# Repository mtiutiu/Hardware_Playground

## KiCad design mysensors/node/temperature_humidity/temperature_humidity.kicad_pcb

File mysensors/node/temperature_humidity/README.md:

#### Mysensors RFM69 temperature & humidity node

##### 3D renderings of pcb

Top view | Bottom view
------------ | -------------
 |

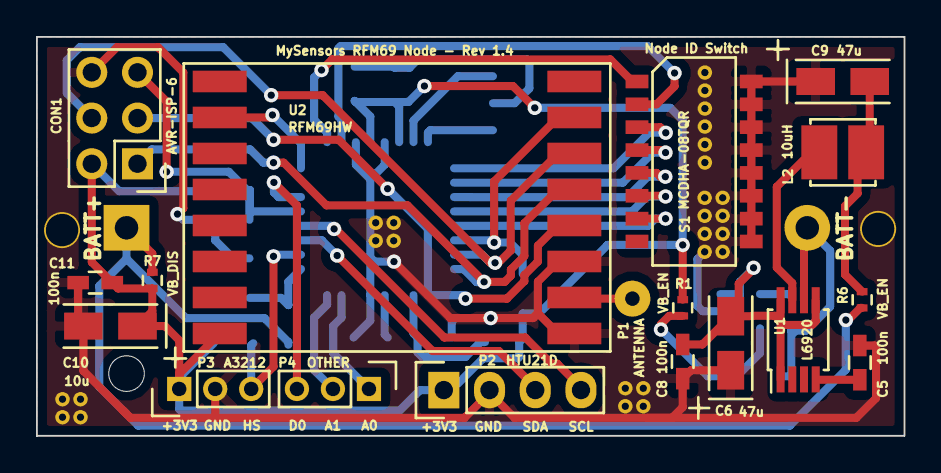
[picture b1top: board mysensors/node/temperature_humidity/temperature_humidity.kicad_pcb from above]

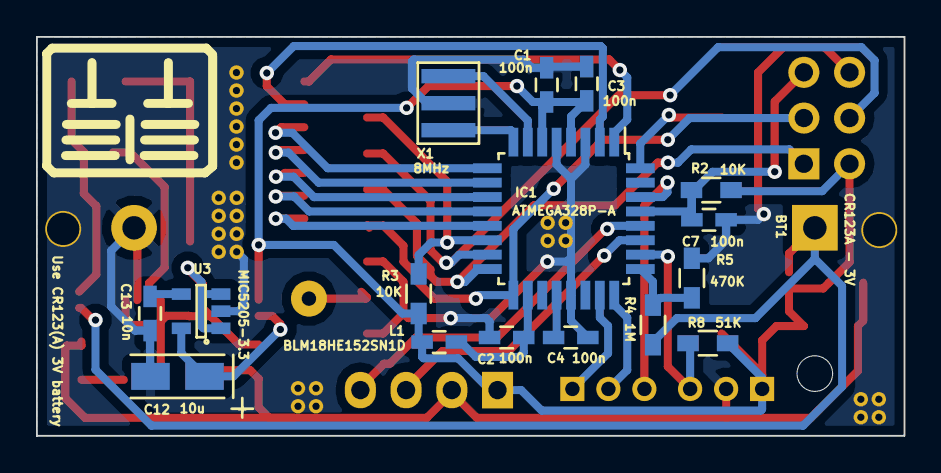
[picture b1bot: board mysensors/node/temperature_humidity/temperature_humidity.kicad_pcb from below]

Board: 2 copper layers, 48.2 x 22.2 mm, 35 parts (17 on the bottom side), 34 nets.

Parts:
BT1: CR123A - 3V; CR123_holder
C1, C2, C3, C4, C5, C7, C8, C11: 100n; C_0603_HandSoldering
C6, C9: 47u; TantalC_SizeA_EIA-3216_Wave
C10, C12: 10u; TantalC_SizeA_EIA-3216_Wave
C13: 10n; C_0603_HandSoldering
CON1: AVR-ISP-6; Pin_Header_Straight_2x03
IC1: ATMEGA328P-A; TQFP-32_7x7mm_Pitch0.8mm
L1: BLM18HE152SN1D; C_0603_HandSoldering
L2: 10uH; DLJ-3015
P1: ANTENNA; SolderWirePad_single_0-8mmDrill
P2: HTU21D; Pin_Header_Straight_1x04
P3: A3212; Pin_Header_Straight_1x03_Pitch2.00mm
P4: OTHER; Pin_Header_Straight_1x03_Pitch2.00mm
R1, R6: VB_EN; R_0402
R2, R3: 10K; R_0603_HandSoldering
R4: 1M; R_0603_HandSoldering
R5: 470K; R_0603_HandSoldering
R7: VB_DIS; R_0402
R8: 51K; R_0603_HandSoldering
S1: MCDHA-08TQR; DIPSWITCH_SMD_1.27-16
U1: L6920; MSOP-8_3x3mm_Pitch0.65mm
U2: RFM69HW; RFM69HW_SMD_Handsoldering
U3: MIC5205-3.3; SOT-23-5
X1: 8MHz; ZTTCR-3

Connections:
+3V3: C1.1, C3.2, C10.1, C11.1, CON1.2, IC1.4, IC1.6, L1.1, P2.1, P3.1, R1.2, R2.1, R3.2, R7.1, R8.1, U2.8
/A0: IC1.23, P4.1
/A1: IC1.24, P4.2
/C0: IC1.1, S1.1
/C1: IC1.2, S1.2
/C2: IC1.9, S1.3
/C3: IC1.10, S1.4
/C4: IC1.11, S1.5
/C5: IC1.12, S1.6
/C6: IC1.13, S1.7
/D0: IC1.30, P4.3
/HALL_SENSOR: IC1.26, P3.3, R8.2
/INT: IC1.32, U2.2
/MISO: CON1.1, IC1.16, U2.13
/MOSI: CON1.4, IC1.15, U2.14
/RESET: C7.2, CON1.5, IC1.29, R2.2
/SCK: CON1.3, IC1.17, U2.12
/SCL: IC1.28, P2.4
/SDA: IC1.27, P2.3
/SS: IC1.14, R3.1, U2.15
/V_BATT: IC1.25, R4.1, R5.2
/V_BOOST_IN: C9.2, L2.2, R6.2
GND: BT1.2, C1.2, C2.1, C3.1, C4.1, C5.2, C6.1, C7.1, C8.2, C9.1, C10.2, C11.2, C12.2, C13.2, CON1.6, IC1.3, IC1.5, IC1.21, P2.2, P3.2, R5.1, S1.9, S1.10, S1.11, S1.12, S1.13, S1.14, S1.15, S1.16, U1.6, U2.9, U2.11, U3.2, X1.3
unnamed: BT1.1, R4.2, R6.1, R7.2
unnamed: C2.2, IC1.18, L1.2
unnamed: C4.2, IC1.20
unnamed: C5.1, U1.4
unnamed: C6.2, C8.1, U1.1, U1.5, U1.8, U3.1, U3.3
unnamed: C12.1, R1.1, U3.5
unnamed: C13.1, U3.4
unnamed: IC1.7, X1.2
unnamed: IC1.8, X1.1
unnamed: L2.1, U1.7
unnamed: P1.1, U2.10

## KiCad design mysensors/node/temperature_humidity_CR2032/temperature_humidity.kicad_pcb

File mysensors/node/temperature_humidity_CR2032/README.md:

## Mysensors RFM69W temperature/humidity node(CR2032)

##### 3D renderings of pcb

Top view | Bottom view
------------ | -------------
 | 

**Description:**

This is a Mysensors node using **RFM69W** radio module and **Si7021** temperature/humidity sensor. 

**Key Features:**

 - **Si7021** temperature/humidity sensor
 - **ATSHA204A** for signing
 - **AT25DF512C-SSHN-B** SPI flash module for OTA
 - **MySensors** ready(**Atmega328p** + **RFM69W**)
 - **DC-DC boost** converter(**NCP1402** based) - can be bypassed using the on board jumpers
 - **Small** board(**36mm diameter**) using a **CR2032** coin cell

**Work progress:**
 1. Test/verify the pcb board correctness(from both electrical and mechanical point of views) - **TO DO**
 2. Produce the initial PCB's using some external PCB manufacturer
 3. Components assembly(soldering)
 4. Upload Mysensors temperature/humidity node sketch code
 5. Verify the real board with running code
 6. Code optimizations for low power operation
 7. Create project enclosure using a 3D printer

**Note: Work in progress(schematic/pcb will change).**

**HW Revisions:**
 - 0.1 - initial design
 - 0.2 - added option to bypass step-up converter using jumpers

**Credits:**
  
  All credits go to **MySensors** team for the great work and to the opensource community

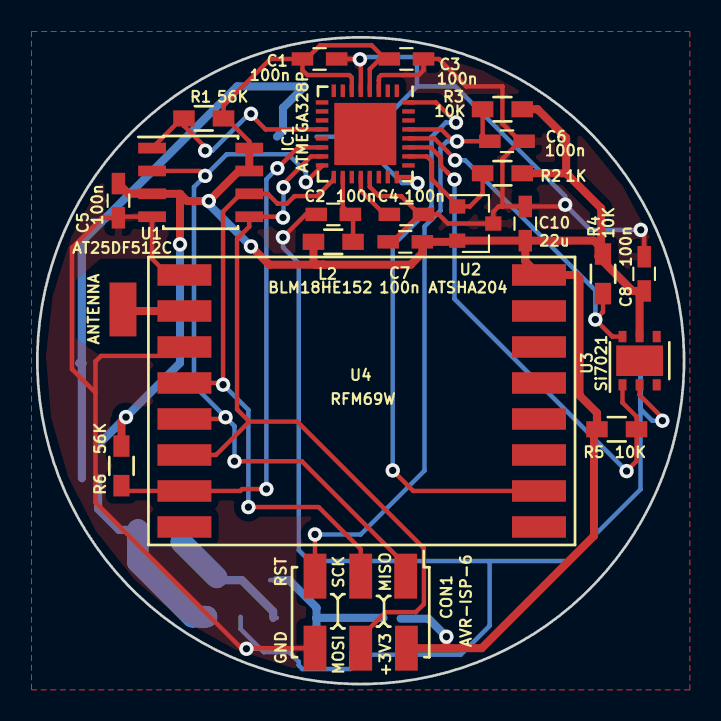
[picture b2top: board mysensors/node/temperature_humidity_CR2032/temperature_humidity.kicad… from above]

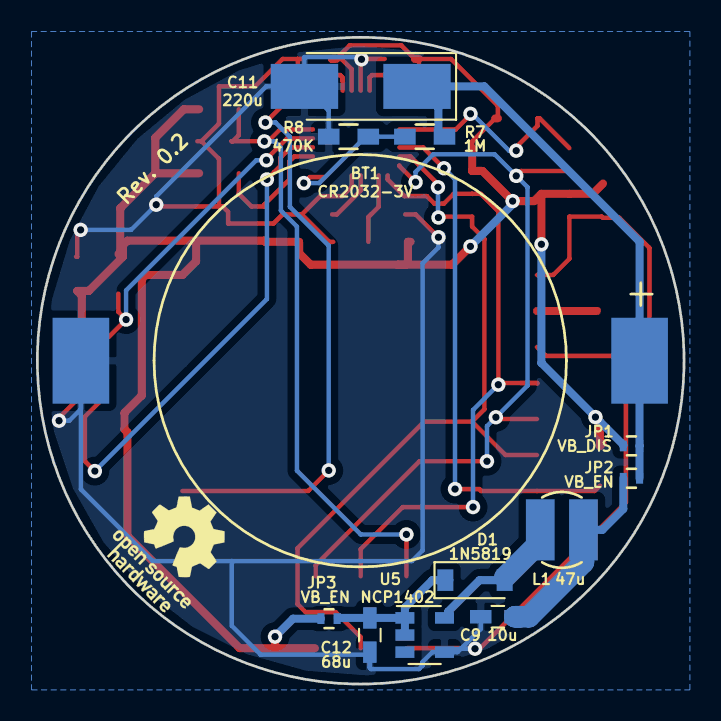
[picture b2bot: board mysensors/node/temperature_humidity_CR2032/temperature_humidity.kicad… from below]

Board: 2 copper layers, 35.9 x 35.9 mm, 35 parts (12 on the bottom side), 20 nets.

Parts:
BT1: CR2032-3V; CR2032_BATT-HOLDER_SMT_H2
C1, C2, C3, C4, C5, C6, C7, C8: 100n; C_0603_HandSoldering
C9: 10u; C_0603_HandSoldering
C10: 22u; C_0603_HandSoldering
C11: 220u; CP_Tantalum_Case-C_EIA-6032-28_Hand
C12: 68u; C_0603_HandSoldering
CON1: AVR-ISP-6; AVR_ISP_SMT_Small_02x03
D1: 1N5819; D_SOD-123
IC1: ATMEGA328P; QFN-32-1EP_5x5mm_Pitch0.5mm
JP1, JP3: VB_EN; R_0402
JP2: VB_DIS; R_0402
L1: 47u; SDR0302
L2: BLM18HE152; R_0603_HandSoldering
P1: ANTENNA; 1pin_smd_2mm
R1, R6: 56K; R_0603_HandSoldering
R2: 1K; R_0603_HandSoldering
R3, R4, R5: 10K; R_0603_HandSoldering
R7: 1M; R_0603_HandSoldering
R8: 470K; R_0603_HandSoldering
U1: AT25DF512C; SOIC-8_3.9x4.9mm_Pitch1.27mm
U2: ATSHA204; SOT-23
U3: Si7021; DFN-6-1EP_3x3mm_Pitch0.95mm
U4: RFM69W; RFM69HW_SMD_Handsoldering
U5: NCP1402; SOT-23-5

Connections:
+3V3: C1.1, C3.2, C5.2, C7.1, C8.1, C10.1, CON1.2, IC1.4, IC1.6, JP2.2, JP3.2, L2.2, R1.2, R2.2, R3.1, R4.2, R5.2, R6.2, U1.3, U1.7, U1.8, U2.2, U3.5, U4.8
/ATSHA204A: IC1.26, R2.1, U2.1
/MISO: CON1.1, IC1.16, U1.2, U4.13
/MOSI: CON1.4, IC1.15, U1.5, U4.14
/RFM69W_INT: IC1.32, U4.2
/RFM69W_SS: IC1.14, R6.1, U4.15
/RST: C6.2, CON1.5, IC1.29, R3.2
/SCK: CON1.3, IC1.17, U1.6, U4.12
/SI7021_SCL: IC1.28, R4.1, U3.6
/SI7021_SDA: IC1.27, R5.1, U3.1
/SPI_FLASH_SS: IC1.12, R1.1, U1.1
/VB_IN: C9.2, JP1.1, L1.1
/V_BATT_MON: IC1.24, R7.1, R8.2
GND: BT1.2, C1.2, C2.1, C3.1, C4.1, C5.1, C6.1, C7.2, C8.2, C9.1, C10.2, C11.2, C12.1, CON1.6, IC1.3, IC1.5, IC1.21, R8.1, U1.4, U2.3, U3.2, U4.9, U4.11, U5.4
unnamed: BT1.1, C11.1, JP1.2, JP2.1, R7.2
unnamed: C2.2, IC1.18, L2.1
unnamed: C4.2, IC1.20
unnamed: C12.2, D1.1, JP3.1, U5.1, U5.2
unnamed: D1.2, L1.2, U5.5
unnamed: P1.1, U4.10

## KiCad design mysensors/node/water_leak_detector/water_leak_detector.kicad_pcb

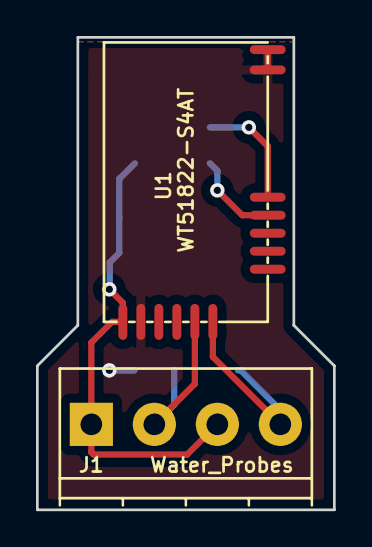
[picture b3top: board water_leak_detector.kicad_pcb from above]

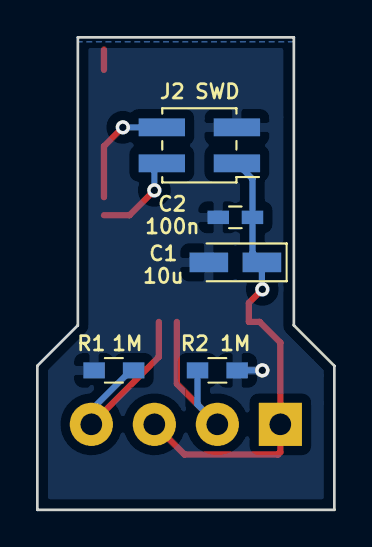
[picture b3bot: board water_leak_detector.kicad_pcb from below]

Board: 2 copper layers, 16.5 x 26.2 mm, 7 parts (5 on the bottom side), 6 nets.

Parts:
C1: 10u; CP_Tantalum_Case-A_EIA-3216-18_Wave
C2: 100n; C_0603_HandSoldering
J1: Water_Probes; TerminalBlock_Pheonix_PT-3.5mm_4pol
J2: SWD; Pin_Header_Straight_2x02_Pitch2.00mm_SMD
R1, R2: 1M; R_0603_HandSoldering
U1: WT51822-S4AT

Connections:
+3V3: C1.1, C2.1, J1.1, J1.3, J2.1, U1.1
/SWCLK: J2.2, U1.10
/SWDIO: J2.4, U1.11
GND: C1.2, C2.2, J2.3, R1.2, R2.2, U1.2, U1.12, U1.13
unnamed: J1.2, R2.1, U1.5
unnamed: J1.4, R1.1, U1.6

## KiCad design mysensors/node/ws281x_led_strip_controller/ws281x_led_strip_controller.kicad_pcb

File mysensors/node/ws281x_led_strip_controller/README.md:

## Mysensors RFM69W WS281x LED strip controller

##### 3D renderings of pcb

Top view | Bottom view
------------ | -------------
 | 

**Description:**

This is a Mysensors RFM69W RGB controller node for controlling a WS281x LED strip

**Key Features:**

 - **AT25DF512C-SSHN-B** SPI flash module for OTA
 - **ATSHA204A** for signing
 - **MySensors** ready(Atmega644P + RFM69W)

**Work progress:**

 1. Test/verify the pcb board correctness(from both electrical and mechanical point of views) - **IN PROGRESS**
 2. Produce the initial PCB's using some external PCB manufacturer
 3. Components assembly(soldering)
 4. Create MySensors sketch code
 5. Verify the real board with running code

**Note: Work in progress(schematic/pcb will change).**

**HW Revisions:**
 - 0.1 - initial hw design
 - 0.2 - replaced atmega328p with atmega644p for more RAM/Flash

The only thing I ask if using this project is to at least mention my name and if I don't ask too much you can also support my effort using the below button. Thanks.

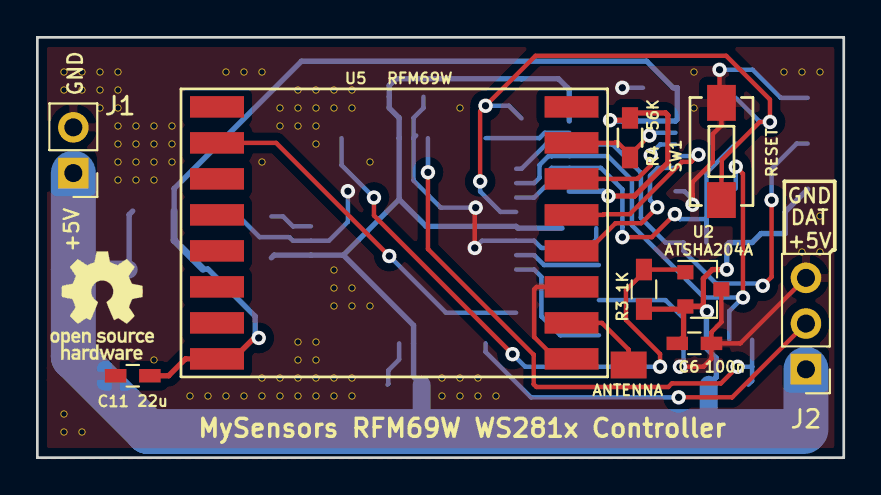
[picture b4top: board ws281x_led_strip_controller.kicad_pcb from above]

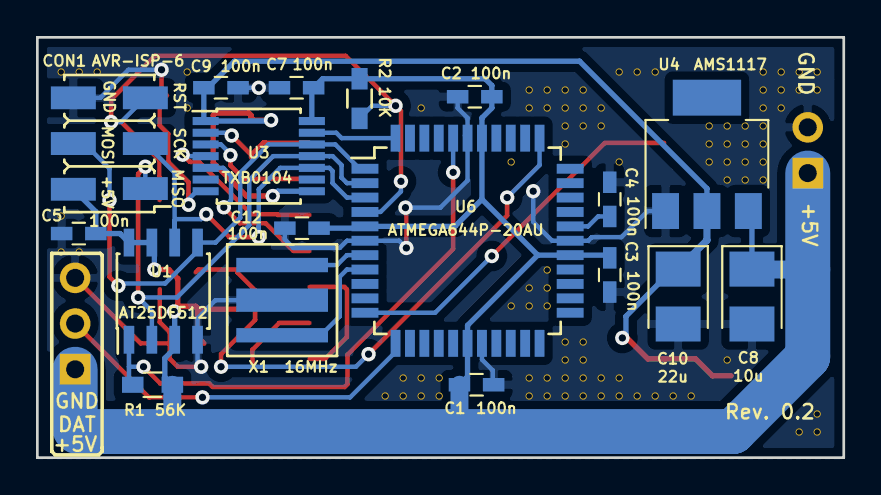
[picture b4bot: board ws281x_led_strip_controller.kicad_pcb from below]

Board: 2 copper layers, 44.8 x 23.4 mm, 117 parts (18 on the bottom side), 20 nets.

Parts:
C1, C2, C3, C4, C5, C6, C7, C9, C12: 100n; C_0603_HandSoldering
C8: 10u; CP_Tantalum_Case-B_EIA-3528-21_Reflow
C10: 22u; CP_Tantalum_Case-B_EIA-3528-21_Reflow
C11: 22u; C_0603_HandSoldering
CON1: AVR-ISP-6; AVR_ISP_SMT_Small_02x03
J1: PWR; Pin_Header_Straight_1x02_Pitch2.54mm
J2: CTRL_OUT; Pin_Header_Straight_1x03_Pitch2.54mm
P1: ANTENNA; 1pin_smd_2mm
R1, R4: 56K; R_0603_HandSoldering
R2: 10K; R_0603_HandSoldering
R3: 1K; R_0603_HandSoldering
SW1: RESET; SW_SPST_EVQPE1
U1: AT25DF512; SOIC-8_3.9x4.9mm_Pitch1.27mm
U2: ATSHA204A; SOT-23
U3: TXB0104; TSSOP-14_4.4x5mm_Pitch0.65mm
U4: AMS1117; SOT-223
U5: RFM69W; RFM69HW_SMD_Handsoldering
U6: ATMEGA644P-20AU; TQFP-44_10x10mm_Pitch0.8mm
V10_2, V10_3, V10_21, V10_22, V11_2, V11_3, V11_22, V12_2, V12_3, V12_4, V13_2, V13_3, V13_4, V13_5, V13_6, V13_7, V13_8, V14_5, V14_6, V14_7, V14_8, V15_5, V15_6, V15_7, V15_8, V15_18, V16_5, V16_6, V16_7, V17_20, V18_20, V19_2, V19_20, V20_2, V20_20, V21_2, V21_7, V21_19, V21_20, V22_4, V22_5, V22_19, V22_20, V23_3, V23_4, V23_5, V23_17, V23_18, V23_19, V23_20, V24_3, V24_4, V24_5, V24_6, V24_17, V24_18, V24_19, V24_20, V25_3, V25_4, V25_13, V25_14, V25_15, V25_19, V25_20, V26_3, V26_4, V26_14, V26_15, V26_19, V26_20, V27_7, V27_15, V31_19, V31_20, V32_4, V32_19, V32_20, V33_19, V33_20, V34_20, V45_2, V45_4, V50_2, V51_2, V51_12, V52_2, V52_10, V52_12: AUTO_VIA; VIA_MATRIX
X1: 16MHz; ZTTCS-3

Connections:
+3V3: C9.2, C10.1, C11.1, R4.2, U3.1, U3.8, U4.2, U5.8
+5V: C1.2, C2.2, C3.2, C5.1, C6.1, C7.1, C8.1, C12.2, CON1.2, J1.1, J2.1, R1.2, R2.1, R3.2, U1.3, U1.7, U1.8, U2.2, U3.14, U4.3, U6.5, U6.17, U6.27, U6.38
/ATSHA204A: R3.1, U2.1, U6.34
/D_OUT: J2.2, U6.12
/MISO: CON1.1, U1.2, U3.11, U6.2
/MOSI: CON1.4, U1.5, U3.12, U6.1
/RFM69W_INT: U5.2, U6.11
/RFM69W_SS: U3.13, U6.44
/RST: CON1.5, R2.2, SW1.1, U6.4
/SCK: CON1.3, U1.6, U3.10, U6.3
/SPI_FLASH_SS: R1.1, U1.1, U6.40
GND: C1.1, C2.1, C3.1, C4.1, C5.2, C6.2, C7.2, C8.2, C9.1, C10.2, C11.2, C12.1, CON1.6, J1.2, J2.3, SW1.2, U1.4, U2.3, U3.7, U4.1, U5.9, U5.11, U6.6, U6.18, U6.28, U6.39, V10_2.1, V10_3.1, V10_21.1, V10_22.1, V11_2.1, V11_3.1, V11_22.1, V12_2.1, V12_3.1, V12_4.1, V13_2.1, V13_3.1, V13_4.1, V13_5.1, V13_6.1, V13_7.1, V13_8.1, V14_5.1, V14_6.1, V14_7.1, V14_8.1, V15_5.1, V15_6.1, V15_7.1, V15_8.1, V15_18.1, V16_5.1, V16_6.1, V16_7.1, V17_20.1, V18_20.1, V19_2.1, V19_20.1, V20_2.1, V20_20.1, V21_2.1, V21_7.1, V21_19.1, V21_20.1, V22_4.1, V22_5.1, V22_19.1, V22_20.1, V23_3.1, V23_4.1, V23_5.1, V23_17.1, V23_18.1, V23_19.1, V23_20.1, V24_3.1, V24_4.1, V24_5.1, V24_6.1, V24_17.1, V24_18.1, V24_19.1, V24_20.1, V25_3.1, V25_4.1, V25_13.1, V25_14.1, V25_15.1, V25_19.1, V25_20.1, V26_3.1, V26_4.1, V26_14.1, V26_15.1, V26_19.1, V26_20.1, V27_7.1, V27_15.1, V31_19.1, V31_20.1, V32_4.1, V32_19.1, V32_20.1, V33_19.1, V33_20.1, V34_20.1, V45_2.1, V45_4.1, V50_2.1, V51_2.1, V51_12.1, V52_2.1, V52_10.1, V52_12.1, X1.2
unnamed: C4.2, U6.29
unnamed: P1.1, U5.10
unnamed: R4.1, U3.2, U5.15
unnamed: U3.3, U5.14
unnamed: U3.4, U5.13
unnamed: U3.5, U5.12
unnamed: U6.7, X1.1
unnamed: U6.8, X1.3

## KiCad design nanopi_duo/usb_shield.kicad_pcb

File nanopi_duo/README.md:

## Nano Pi Duo USB Shield

##### 3D renderings of pcb

Top view | Bottom view
------------ | -------------
 | 

**Description:**

This is a simple USB shield for the Nano Pi Duo Linux SBC

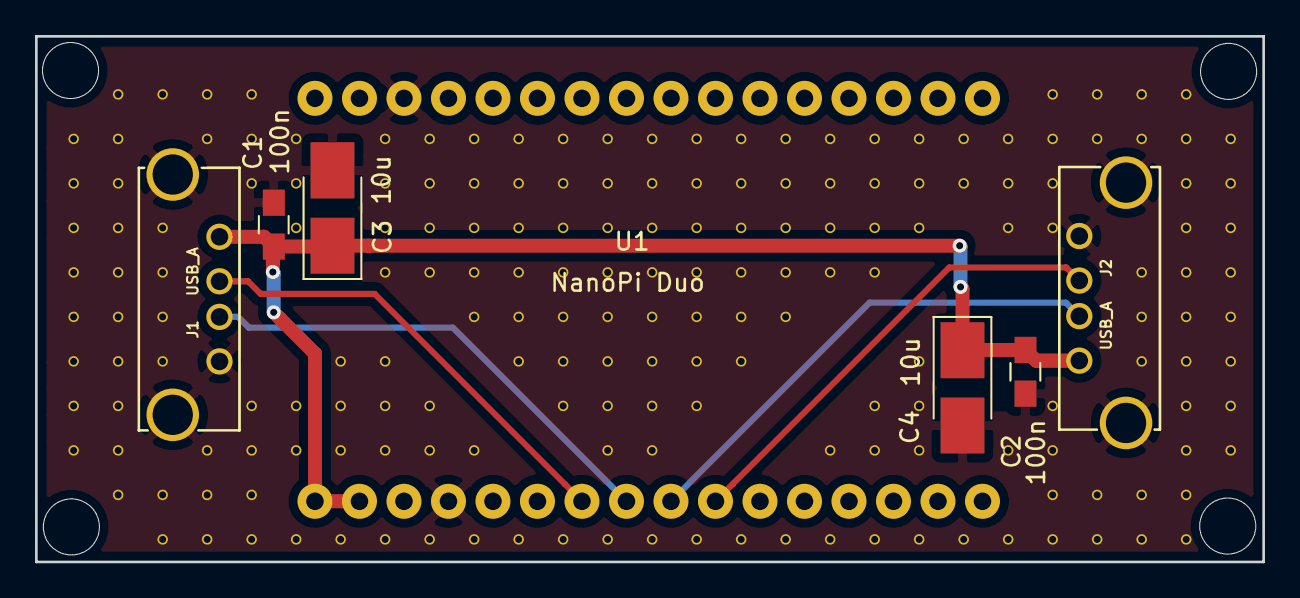
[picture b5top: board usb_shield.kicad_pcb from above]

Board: 2 copper layers, 70.0 x 30.0 mm, 196 parts (0 on the bottom side), 6 nets.

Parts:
C1, C2: 100n; C_0805_HandSoldering
C3, C4: 10u; CP_Tantalum_Case-B_EIA-3528-21_Hand
J1, J2: USB_A; USB_A_top
U1: NanoPi Duo; nano_pi_duo_usb_shield
V4_4, V4_5, V4_6, V4_7, V4_8, V4_9, V4_10, V4_11, V5_3, V5_4, V5_5, V5_6, V5_7, V5_8, V5_9, V5_10, V5_11, V5_12, V6_3, V6_6, V6_7, V6_8, V6_9, V6_12, V6_13, V7_3, V7_4, V7_11, V7_12, V7_13, V8_3, V8_4, V8_5, V8_10, V8_11, V8_12, V8_13, V9_4, V9_5, V9_6, V9_10, V9_11, V9_13, V10_9, V10_10, V10_11, V10_13, V11_4, V11_5, V11_6, V11_7, V11_9, V11_10, V11_11, V11_13, V12_4, V12_5, V12_6, V12_7, V12_10, V12_11, V12_13, V13_4, V13_5, V13_6, V13_7, V13_8, V13_11, V13_13, V14_4, V14_5, V14_6, V14_7, V14_8, V14_9, V14_13, V15_4, V15_5, V15_6, V15_7, V15_8, V15_9, V15_10, V15_13, V16_4, V16_5, V16_6, V16_7, V16_8, V16_9, V16_10, V16_11, V16_13, V17_4, V17_5, V17_6, V17_7, V17_8, V17_9, V17_10, V17_11, V17_13, V18_4, V18_5, V18_6, V18_7, V18_8, V18_9, V18_10, V18_13, V19_4, V19_5, V19_6, V19_7, V19_8, V19_9, V19_13, V20_4, V20_5, V20_6, V20_7, V20_8, V20_13, V21_4, V21_5, V21_6, V21_7, V21_11, V21_13, V22_4, V22_5, V22_6, V22_7, V22_10, V22_11, V22_13, V23_4, V23_5, V23_6, V23_9, V23_10, V23_11, V23_13, V24_4, V24_5, V24_13, V25_4, V25_5, V25_6, V25_11, V25_13, V26_3, V26_4, V26_5, V26_6, V26_10, V26_11, V26_12, V26_13, V27_3, V27_4, V27_12, V27_13, V28_3, V28_4, V28_7, V28_8, V28_9, V28_12, V28_13, V29_3, V29_4, V29_5, V29_6, V29_7, V29_8, V29_9, V29_10, V29_11, V29_12, V29_13, V30_4, V30_5, V30_6, V30_7, V30_8, V30_9, V30_10, V30_11: AUTO_VIA; VIA_MATRIX

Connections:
+5V: C1.1, C2.1, C3.1, C4.1, J1.1, J2.1, U1.31, U1.32
/DM2: J2.2, U1.24
/DM3: J1.2, U1.26
/DP2: J2.3, U1.23
/DP3: J1.3, U1.25
GND: C1.2, C2.2, C3.2, C4.2, J1.4, J1.5, J2.4, J2.5, U1.3, U1.29, V4_4.1, V4_5.1, V4_6.1, V4_7.1, V4_8.1, V4_9.1, V4_10.1, V4_11.1, V5_3.1, V5_4.1, V5_5.1, V5_6.1, V5_7.1, V5_8.1, V5_9.1, V5_10.1, V5_11.1, V5_12.1, V6_3.1, V6_6.1, V6_7.1, V6_8.1, V6_9.1, V6_12.1, V6_13.1, V7_3.1, V7_4.1, V7_11.1, V7_12.1, V7_13.1, V8_3.1, V8_4.1, V8_5.1, V8_10.1, V8_11.1, V8_12.1, V8_13.1, V9_4.1, V9_5.1, V9_6.1, V9_10.1, V9_11.1, V9_13.1, V10_9.1, V10_10.1, V10_11.1, V10_13.1, V11_4.1, V11_5.1, V11_6.1, V11_7.1, V11_9.1, V11_10.1, V11_11.1, V11_13.1, V12_4.1, V12_5.1, V12_6.1, V12_7.1, V12_10.1, V12_11.1, V12_13.1, V13_4.1, V13_5.1, V13_6.1, V13_7.1, V13_8.1, V13_11.1, V13_13.1, V14_4.1, V14_5.1, V14_6.1, V14_7.1, V14_8.1, V14_9.1, V14_13.1, V15_4.1, V15_5.1, V15_6.1, V15_7.1, V15_8.1, V15_9.1, V15_10.1, V15_13.1, V16_4.1, V16_5.1, V16_6.1, V16_7.1, V16_8.1, V16_9.1, V16_10.1, V16_11.1, V16_13.1, V17_4.1, V17_5.1, V17_6.1, V17_7.1, V17_8.1, V17_9.1, V17_10.1, V17_11.1, V17_13.1, V18_4.1, V18_5.1, V18_6.1, V18_7.1, V18_8.1, V18_9.1, V18_10.1, V18_13.1, V19_4.1, V19_5.1, V19_6.1, V19_7.1, V19_8.1, V19_9.1, V19_13.1, V20_4.1, V20_5.1, V20_6.1, V20_7.1, V20_8.1, V20_13.1, V21_4.1, V21_5.1, V21_6.1, V21_7.1, V21_11.1, V21_13.1, V22_4.1, V22_5.1, V22_6.1, V22_7.1, V22_10.1, V22_11.1, V22_13.1, V23_4.1, V23_5.1, V23_6.1, V23_9.1, V23_10.1, V23_11.1, V23_13.1, V24_4.1, V24_5.1, V24_13.1, V25_4.1, V25_5.1, V25_6.1, V25_11.1, V25_13.1, V26_3.1, V26_4.1, V26_5.1, V26_6.1, V26_10.1, V26_11.1, V26_12.1, V26_13.1, V27_3.1, V27_4.1, V27_12.1, V27_13.1, V28_3.1, V28_4.1, V28_7.1, V28_8.1, V28_9.1, V28_12.1, V28_13.1, V29_3.1, V29_4.1, V29_5.1, V29_6.1, V29_7.1, V29_8.1, V29_9.1, V29_10.1, V29_11.1, V29_12.1, V29_13.1, V30_4.1, V30_5.1, V30_6.1, V30_7.1, V30_8.1, V30_9.1, V30_10.1, V30_11.1

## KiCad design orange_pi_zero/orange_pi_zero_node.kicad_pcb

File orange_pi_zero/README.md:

## Orange Pi Zero Shield(HAT)

##### 3D renderings of pcb

Top view | Bottom view
------------ | -------------
 | 

**Description:**

This is a shield(or HAT) for the Orange Pi Zero Linux SBC

**Key Features:**

 - **DS18B20** temperature/humidity sensor
 - **OLED Display(SSD1306 - 128x32)**
 - **LED Bargraph**

**Work progress:**
 1. Test/verify the pcb board correctness(from both electrical and mechanical point of views) - **DONE**
 2. Produce the initial PCB's using some external PCB manufacturer - **IN PROGRESS**
 3. Components assembly(soldering)
 4. Verify the real board with running code
 5. Create project enclosure using a 3D printer

**HW Revisions:**
 - 0.1 - initial design

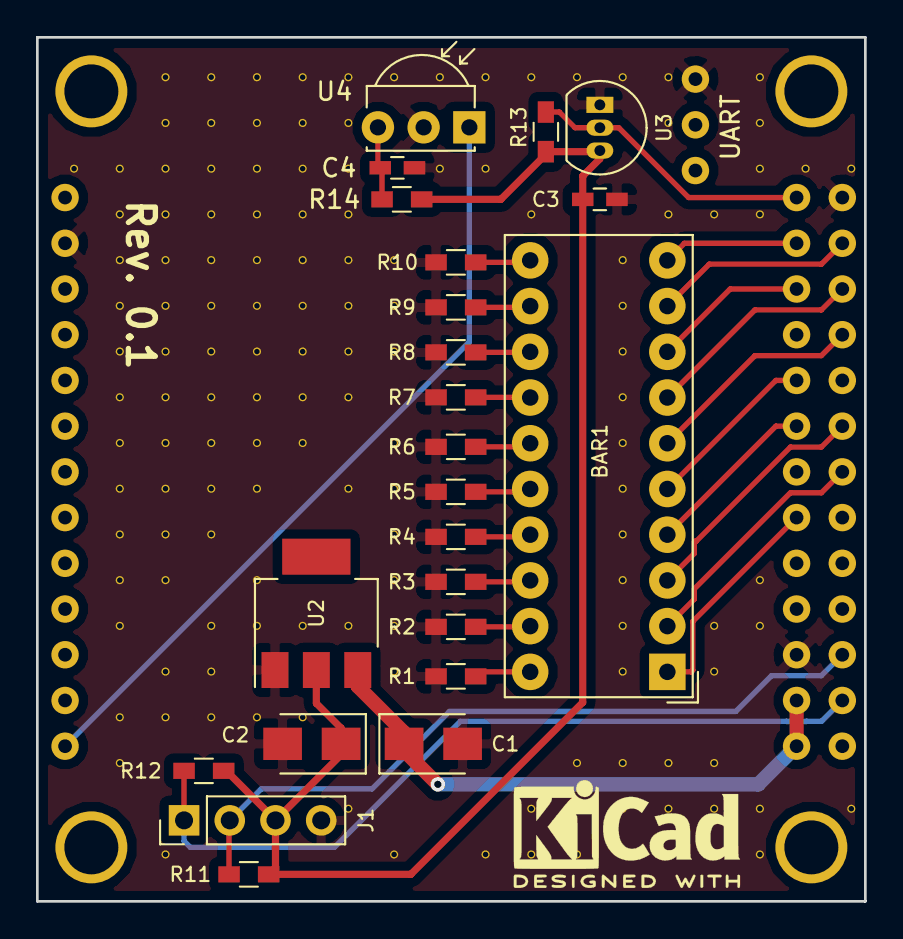
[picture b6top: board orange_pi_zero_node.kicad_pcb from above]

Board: 2 copper layers, 46.0 x 48.0 mm, 163 parts (0 on the bottom side), 28 nets.

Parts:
BAR1: HDSP-4850_2; HDSP-4850
C1, C2: 22u; CP_Tantalum_Case-B_EIA-3528-21_Wave
C3, C4: 100n; C_0603_HandSoldering
J1: Conn_01x04; Pin_Header_Straight_1x04_Pitch2.54mm
R1, R2, R3, R4, R5, R6, R7, R8, R9, R10: 330; R_0603_HandSoldering
R11, R12, R13: 4K7; R_0603_HandSoldering
R14: 100; R_0603_HandSoldering
U1: orange_pi_zero; orangepi-zero
U2: AMS1117-3.3; SOT-223
U3: DS18B20; TO-92_Inline_Narrow_Oval
U4: TSOP343xx; IRReceiver_Vishay_MOLD-3pin
V1_3, V2_3, V2_4, V2_5, V2_6, V2_7, V2_8, V2_9, V2_10, V2_11, V2_12, V2_13, V2_15, V2_16, V3_1, V3_2, V3_3, V3_4, V3_5, V3_6, V3_7, V3_8, V3_9, V3_10, V3_11, V3_12, V3_14, V3_15, V3_18, V4_1, V4_2, V4_3, V4_4, V4_5, V4_6, V4_7, V4_8, V4_9, V4_10, V4_11, V4_13, V4_14, V4_15, V5_1, V5_2, V5_3, V5_4, V5_5, V5_6, V5_7, V5_8, V5_9, V5_10, V5_12, V5_13, V5_15, V6_1, V6_2, V6_3, V6_4, V6_5, V6_6, V6_7, V6_8, V6_9, V6_13, V6_15, V7_1, V7_2, V7_3, V7_4, V7_5, V7_6, V7_7, V7_8, V7_10, V7_13, V7_17, V8_1, V8_5, V8_6, V8_7, V8_9, V8_10, V8_11, V8_12, V8_13, V8_14, V8_18, V9_1, V9_3, V10_1, V10_3, V10_18, V11_1, V11_4, V11_17, V11_18, V12_1, V12_16, V12_17, V12_18, V13_1, V13_5, V13_6, V13_7, V13_8, V13_9, V13_10, V13_11, V13_12, V13_13, V13_14, V13_16, V13_17, V13_18, V14_1, V14_2, V14_4, V14_16, V14_17, V14_18, V15_4, V15_13, V15_14, V15_16, V15_17, V15_18, V16_1, V16_2, V16_3, V16_4, V16_12, V16_13, V16_17, V16_18, V17_3, V18_3, V18_17: AUTO_VIA; VIA_MATRIX

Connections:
+3V3: C2.1, C3.2, J1.3, R11.2, R12.2, R13.2, R14.2, U2.2, U3.3
+5V: C1.1, U1.102, U1.104, U2.3
GND: C1.2, C2.2, C3.1, C4.1, J1.4, R1.1, R2.1, R3.1, R4.1, R5.1, R6.1, R7.1, R8.1, R9.1, R10.1, U1.2, U1.106, U1.114, U1.120, U1.125, U1.201, U2.1, U3.1, U4.2, V1_3.1, V2_3.1, V2_4.1, V2_5.1, V2_6.1, V2_7.1, V2_8.1, V2_9.1, V2_10.1, V2_11.1, V2_12.1, V2_13.1, V2_15.1, V2_16.1, V3_1.1, V3_2.1, V3_3.1, V3_4.1, V3_5.1, V3_6.1, V3_7.1, V3_8.1, V3_9.1, V3_10.1, V3_11.1, V3_12.1, V3_14.1, V3_15.1, V3_18.1, V4_1.1, V4_2.1, V4_3.1, V4_4.1, V4_5.1, V4_6.1, V4_7.1, V4_8.1, V4_9.1, V4_10.1, V4_11.1, V4_13.1, V4_14.1, V4_15.1, V5_1.1, V5_2.1, V5_3.1, V5_4.1, V5_5.1, V5_6.1, V5_7.1, V5_8.1, V5_9.1, V5_10.1, V5_12.1, V5_13.1, V5_15.1, V6_1.1, V6_2.1, V6_3.1, V6_4.1, V6_5.1, V6_6.1, V6_7.1, V6_8.1, V6_9.1, V6_13.1, V6_15.1, V7_1.1, V7_2.1, V7_3.1, V7_4.1, V7_5.1, V7_6.1, V7_7.1, V7_8.1, V7_10.1, V7_13.1, V7_17.1, V8_1.1, V8_5.1, V8_6.1, V8_7.1, V8_9.1, V8_10.1, V8_11.1, V8_12.1, V8_13.1, V8_14.1, V8_18.1, V9_1.1, V9_3.1, V10_1.1, V10_3.1, V10_18.1, V11_1.1, V11_4.1, V11_17.1, V11_18.1, V12_1.1, V12_16.1, V12_17.1, V12_18.1, V13_1.1, V13_5.1, V13_6.1, V13_7.1, V13_8.1, V13_9.1, V13_10.1, V13_11.1, V13_12.1, V13_13.1, V13_14.1, V13_16.1, V13_17.1, V13_18.1, V14_1.1, V14_2.1, V14_4.1, V14_16.1, V14_17.1, V14_18.1, V15_4.1, V15_13.1, V15_14.1, V15_16.1, V15_17.1, V15_18.1, V16_1.1, V16_2.1, V16_3.1, V16_4.1, V16_12.1, V16_13.1, V16_17.1, V16_18.1, V17_3.1, V18_3.1, V18_17.1
unnamed: BAR1.1, U1.112
unnamed: BAR1.2, U1.113
unnamed: BAR1.3, U1.115
unnamed: BAR1.4, U1.116
unnamed: BAR1.5, U1.118
unnamed: BAR1.6, U1.119
unnamed: BAR1.7, U1.121
unnamed: BAR1.8, U1.122
unnamed: BAR1.9, U1.123
unnamed: BAR1.10, U1.124
unnamed: BAR1.11, R10.2
unnamed: BAR1.12, R9.2
unnamed: BAR1.13, R8.2
unnamed: BAR1.14, R7.2
unnamed: BAR1.15, R6.2
unnamed: BAR1.16, R5.2
unnamed: BAR1.17, R4.2
unnamed: BAR1.18, R3.2
unnamed: BAR1.19, R2.2
unnamed: BAR1.20, R1.2
unnamed: C4.2, R14.1, U4.3
unnamed: J1.1, R12.1, U1.103
unnamed: J1.2, R11.1, U1.105
unnamed: R13.1, U1.126, U3.2
unnamed: U1.13, U4.1
